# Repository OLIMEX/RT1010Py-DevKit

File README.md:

# RT1010Py-DevKit
Development board for RT1010Py board

https://www.olimex.com/Products/MicroPython/RT1010Py-DevKit/open-source-hardware

Features:

* RT1010Py socket connector
* Two UEXT connectors
* Two Relays 10A/250VAC
* USB-C power supply
* Two buttons
* Boot configuration slide switch
* Dimensions: (55 x 75)mm ~ (2.17 x 2.95)"

## Documentation

Check the files in OLIMEX/RT1010Py-DevKit/__DOCUMENTS__ for ressources:

* [RT1010Py-DevKit user manual](DOCUMENTS/RT1010Py-DevKit-user-manual.pdf) (pdf)
* [RT1010Py-DevKit edge connector PinOut](DOCUMENTS/RT1010Py-EVB-edge-connector.jpg) (jpg)
* [RT1010Py-DevKit UEXT PinOut](DOCUMENTS/RT1010Py-EVB-UEXT) (jpg)

See also the [RT1010-Py Microcontroler documentation](https://github.com/OLIMEX/RT1010Py) on its own repository.

## Licenses

* Hardware is released under CERN Open Hardware Licence Version 2 - Strongly Reciprocal, all silkscreen credits to Olimex should remain;
* Software is released under GPL3 Licensee
* Documentation is released under CC BY-SA 4.0

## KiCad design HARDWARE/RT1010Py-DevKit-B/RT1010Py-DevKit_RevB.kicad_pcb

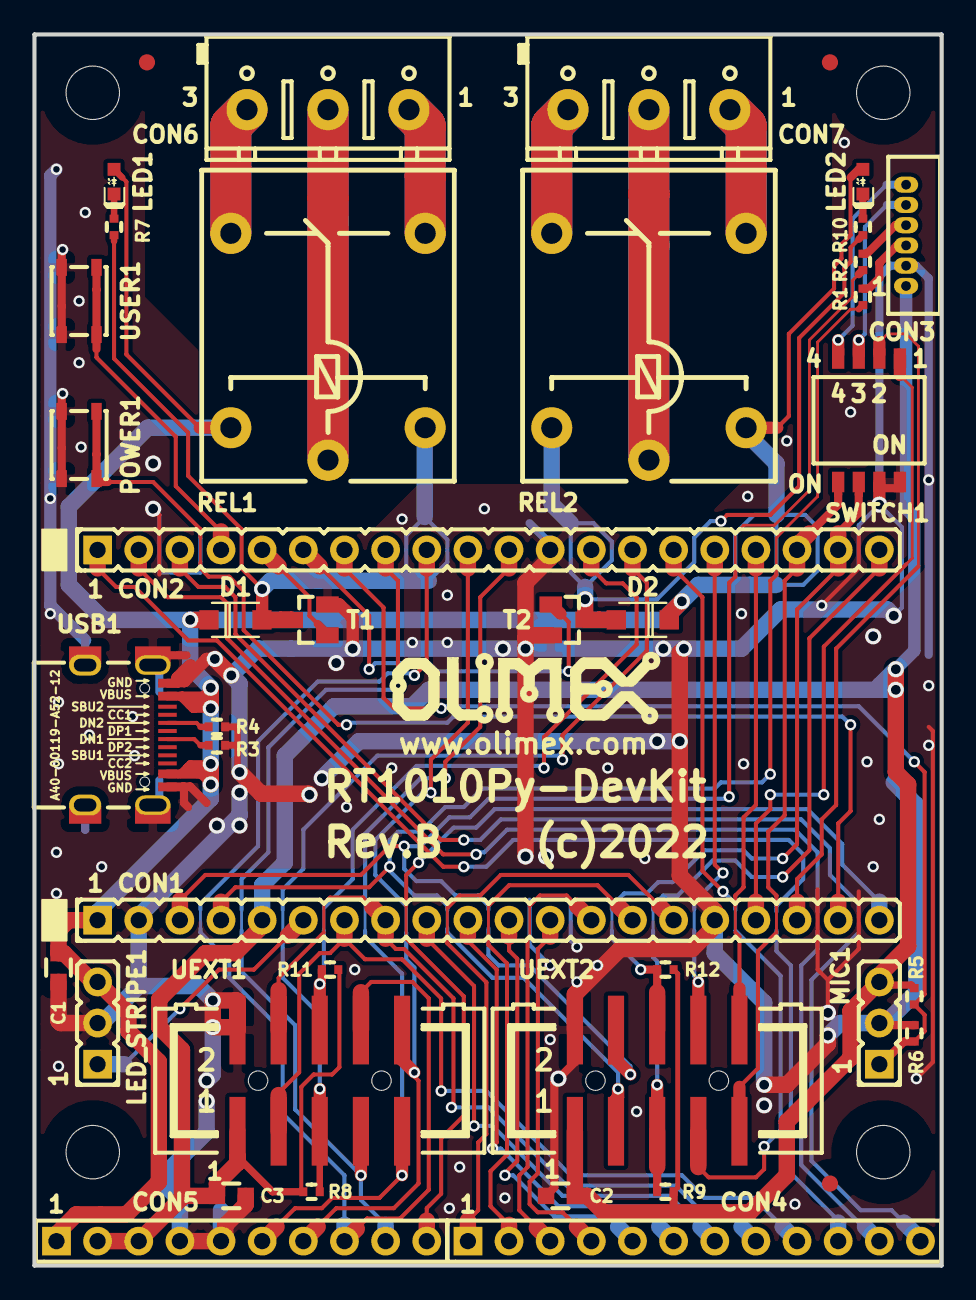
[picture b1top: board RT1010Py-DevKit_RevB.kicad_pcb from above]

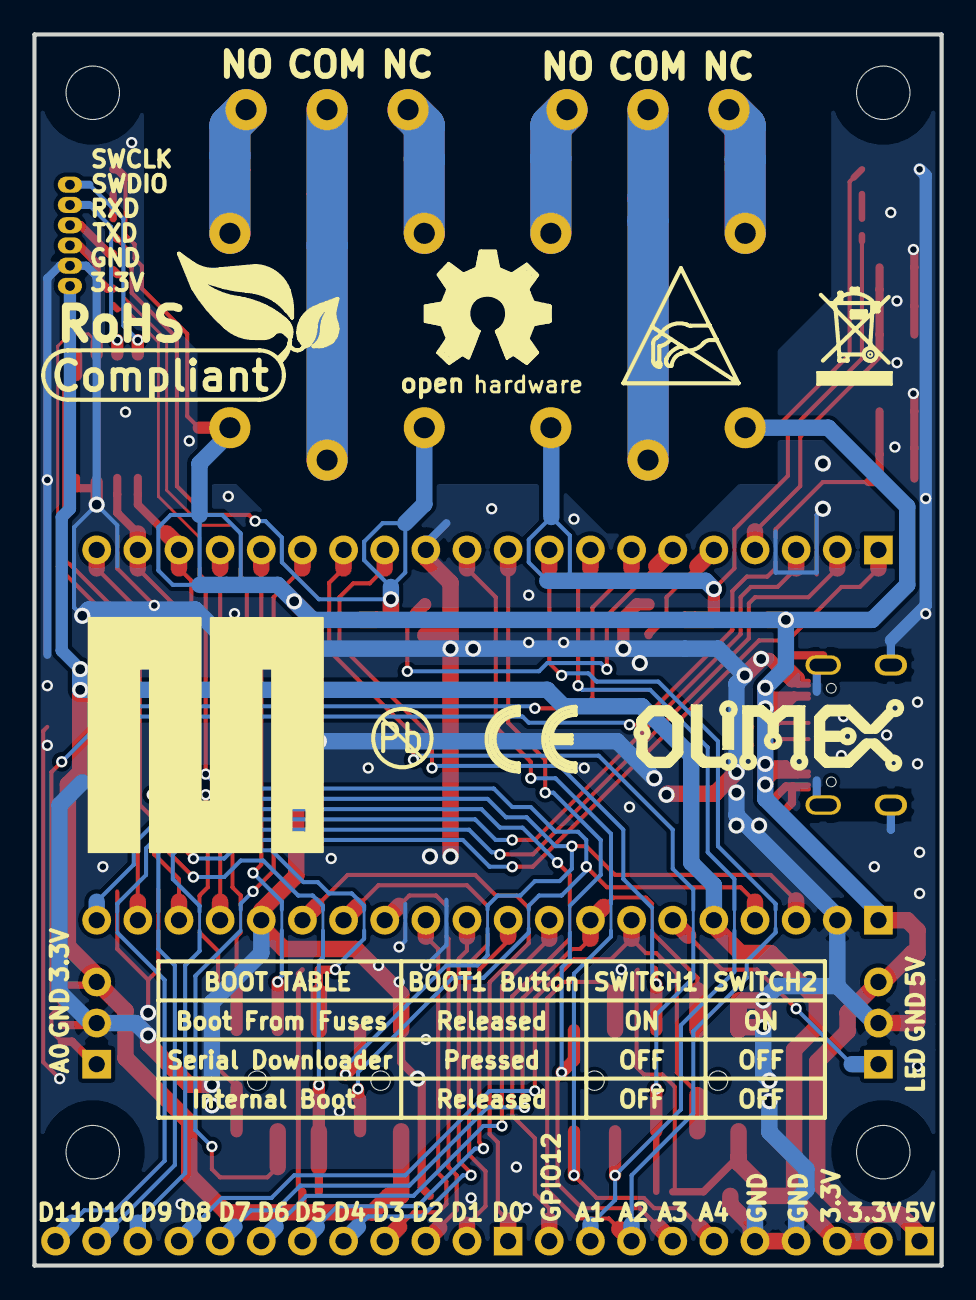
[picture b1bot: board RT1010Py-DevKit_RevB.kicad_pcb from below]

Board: 2 copper layers, 56.0 x 76.0 mm, 54 parts (8 on the bottom side), 54 nets.

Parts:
C1: NA(4.7uF/6.3V); C_0603_5MIL_DWS
C2, C3: 4.7uF/6.3V/0603; C_0603_5MIL_DWS
CE_Sign: CE_Sign
CON1, CON2: PN1X20(F-D-1X20-LF); HN1x20
CON3: NA(WU06S); WU06S
CON4: PN_F-D-1X12-LF; PN1x12
CON5: PN_F-D-1x10-LF; PN1x10
CON6, CON7: DG306-5.0-3P; TB3-5mm
D1, D2: 1N4148W; SOD-123_KA
FID1, FID2, FID3: Fiducial; Fiducial1x3
LED1, LED2: LED/Green/0603; LED_0603_KA
LED_STRIPE1: NA; HN1x3
MH1, MH2, MH3, MH4: Mounting_Hole_NPTH; Mounting_hole_3.3mm
MIC1: NA; HN1x3
MicroPython_Logo: LOGO; MicroPython_Logo
Olimex_Logo, Olimex_Logo1: OLIMEX_LOGO_TB
Open_Hardware: LOGO_OPENHARDWARE_8x8
POWER1: T1107A(6x3,8x2,5MM); YTS-A016-X
R1, R2: NA(220R); R_0402_5MIL_DWS
R3, R4: 5.1K/0402; R_0402_5MIL_DWS
R5, R6: NA(100K); R_0402_5MIL_DWS
R7, R10: 10K/0402; R_0402_5MIL_DWS
R8, R9, R11, R12: 2.2K/0402; R_0402_5MIL_DWS
REL1, REL2: RAS0515; Relay_RAS-05-15
Recycle: LOGO_RECYCLEBIN_1
SWITCH1: DSHP04TS-S; DSHP04TS-S-1.27mm_Half_4_Slide
Sign_Antistatic: Sign_Antistatic
Sign_PB-Free: Sign_PB-Free
Sign_RoHS_1: Sign_RoHS_1
T1, T2: LMUN2211LT1G(SOT-23); SOT23
UEXT1, UEXT2: BH10S(B-D-02x5-LF); GBH-254-SMT-10
USB1: USB-C-16P-F; USB2.0_TYPE-C(A40-00119-A52-12)
USER1: T1107A(6x3,8x2,5MM); YTS-A016-X

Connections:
+3.3V: C2.2, C3.2, CON1.5, CON3.1, CON5.2, CON5.3, MIC1.3, R5.2, R8.2, R9.2, R11.2, R12.2, UEXT1.1, UEXT2.1
+5V: C1.1, CON1.1, CON5.1, D1.1, D2.1, LED1.2, LED2.2, LED_STRIPE1.3, REL1.2, REL2.1, USB1.A4, USB1.A9, USB1.B4, USB1.B9
/BOOTSEL0: CON1.18, SWITCH1.2
/BOOTSEL1: CON1.17, SWITCH1.1
/GPIO2_IO00: CON2.1, CON4.10
/GPIO2_IO01: CON2.2, CON4.11
/GPIO2_IO02: CON2.3, CON4.12
/GPIO2_IO05: CON2.4, USER1.1
/GPIO2_IO12: CON2.5, T1.1
/GPIO2_IO13: CON2.6, T2.1
/GPIO_00: CON1.15, CON4.1
/GPIO_01: CON1.14, CON4.2
/GPIO_02: CON1.13, CON4.3
/GPIO_03: CON1.12, CON4.4
/GPIO_04: CON1.11, CON4.5
/GPIO_05: CON1.10, CON4.6
/GPIO_06: CON1.9, CON4.7
/GPIO_07: CON1.8, CON4.8, UEXT1.4
/GPIO_08: CON1.7, CON4.9, UEXT1.3
/GPIO_11_LED: CON1.6, LED_STRIPE1.1
/GPIO_12: CON1.20, CON5.10
/I2C1_SCL: CON2.20, R9.1, UEXT2.5
/I2C1_SDA: CON2.19, R12.1, SWITCH1.6, UEXT2.6
/I2C2_SCL: CON2.14, R8.1, UEXT1.5
/I2C2_SDA: CON2.13, R11.1, UEXT1.6
/LPSPI1_PCS0: CON2.10, CON5.7, UEXT1.10
/LPSPI1_PCS1: CON2.7, MIC1.1, R5.1, R6.2
/LPSPI1_SCK: CON2.11, CON5.6, UEXT1.9
/LPSPI1_SDI: CON2.8, CON5.9, UEXT1.7
/LPSPI1_SDO: CON2.9, CON5.8, UEXT1.8
/LPSPI2_PCS0: CON2.17, UEXT2.10
/LPSPI2_SCK: CON2.18, SWITCH1.5, UEXT2.9
/LPSPI2_SDI: CON2.15, UEXT2.7
/LPSPI2_SDO: CON2.16, UEXT2.8
/LPUART1_RXD: CON1.3, R2.1, UEXT2.4
/LPUART1_TXD: CON1.4, R1.1, UEXT2.3
/ONOFF: CON1.19, POWER1.1
/T_SWCLK: CON3.6, SWITCH1.4
/T_SWDIO: CON3.5, SWITCH1.3
GND: C1.2, C2.1, C3.1, CON1.2, CON1.16, CON2.12, CON3.2, CON5.4, CON5.5, LED_STRIPE1.2, MIC1.2, POWER1.2, R3.1, R4.1, R6.1, SWITCH1.7, SWITCH1.8, T1.2, T2.2, UEXT1.2, UEXT2.2, USB1.0, USB1.A1, USB1.A12, USB1.B1, USB1.B12, USER1.2
unnamed: CON3.3, R1.2
unnamed: CON3.4, R2.2
unnamed: CON6.1, REL1.NO0
unnamed: CON6.2, REL1.COM0
unnamed: CON6.3, REL1.NC0
unnamed: CON7.1, REL2.NO0
unnamed: CON7.2, REL2.COM0
unnamed: CON7.3, REL2.NC0
unnamed: D1.2, R7.1, REL1.1, T1.3
unnamed: D2.2, R10.1, REL2.2, T2.3
unnamed: LED1.1, R7.2
unnamed: LED2.1, R10.2
unnamed: R3.2, USB1.A7
unnamed: R4.2, USB1.B7

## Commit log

2024-01-15 initial upload
2024-01-15 add user manual
2025-10-24 add user manual source
2025-10-25 Add documentation
2025-10-25 Add Documentation section in README

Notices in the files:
HARDWARE/RT1010Py-DevKit-B/RT1010Py-DevKit_RevB.kicad_pcb:
(c)2022
